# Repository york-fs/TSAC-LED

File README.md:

This board is based on the design by Rootthecause, whos original design can be accessed [here](https://github.com/Rootthecause/HVI)

Changes made (Listed in order to conform to the CERN Open Hardware Licence):
- The two connectors as input has been changed to a single molex microfit plus connector
- The output connector has been replaced with a molex microfit plus equivalent
- The DC/DC converter has been changed to a 12V one, in order for a 12V output
- The board has been restructured and more silkscreen elements have been added

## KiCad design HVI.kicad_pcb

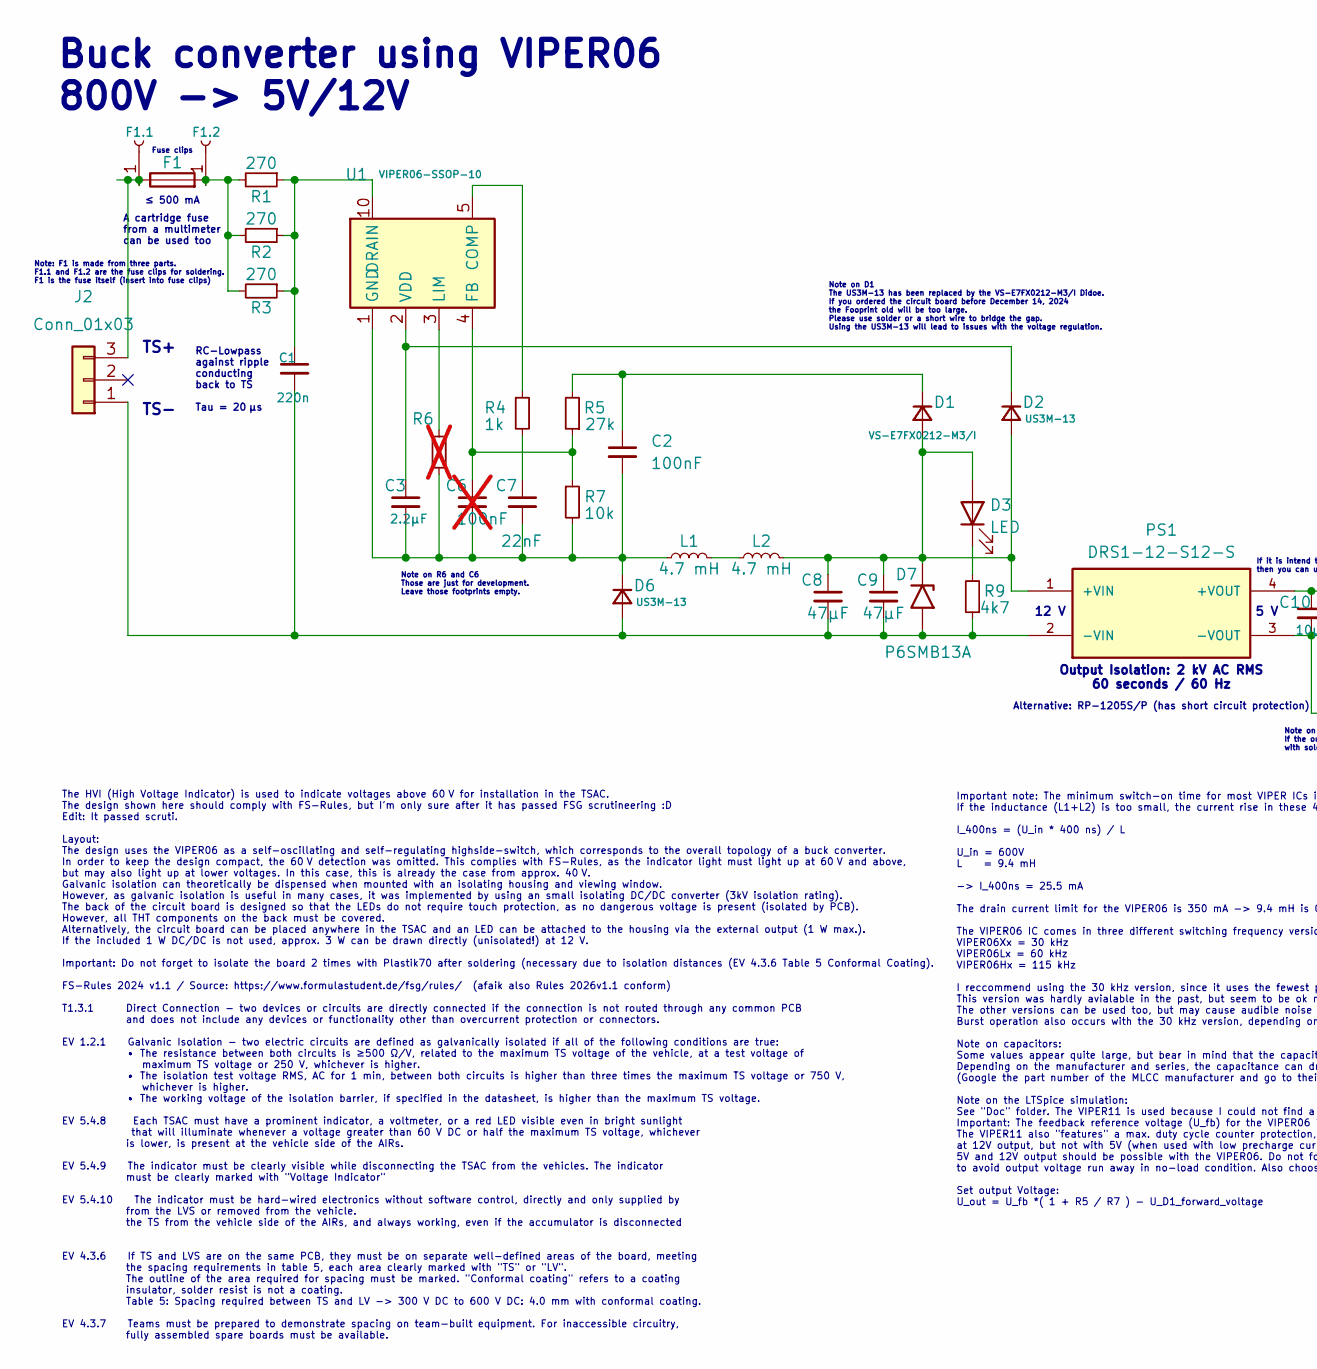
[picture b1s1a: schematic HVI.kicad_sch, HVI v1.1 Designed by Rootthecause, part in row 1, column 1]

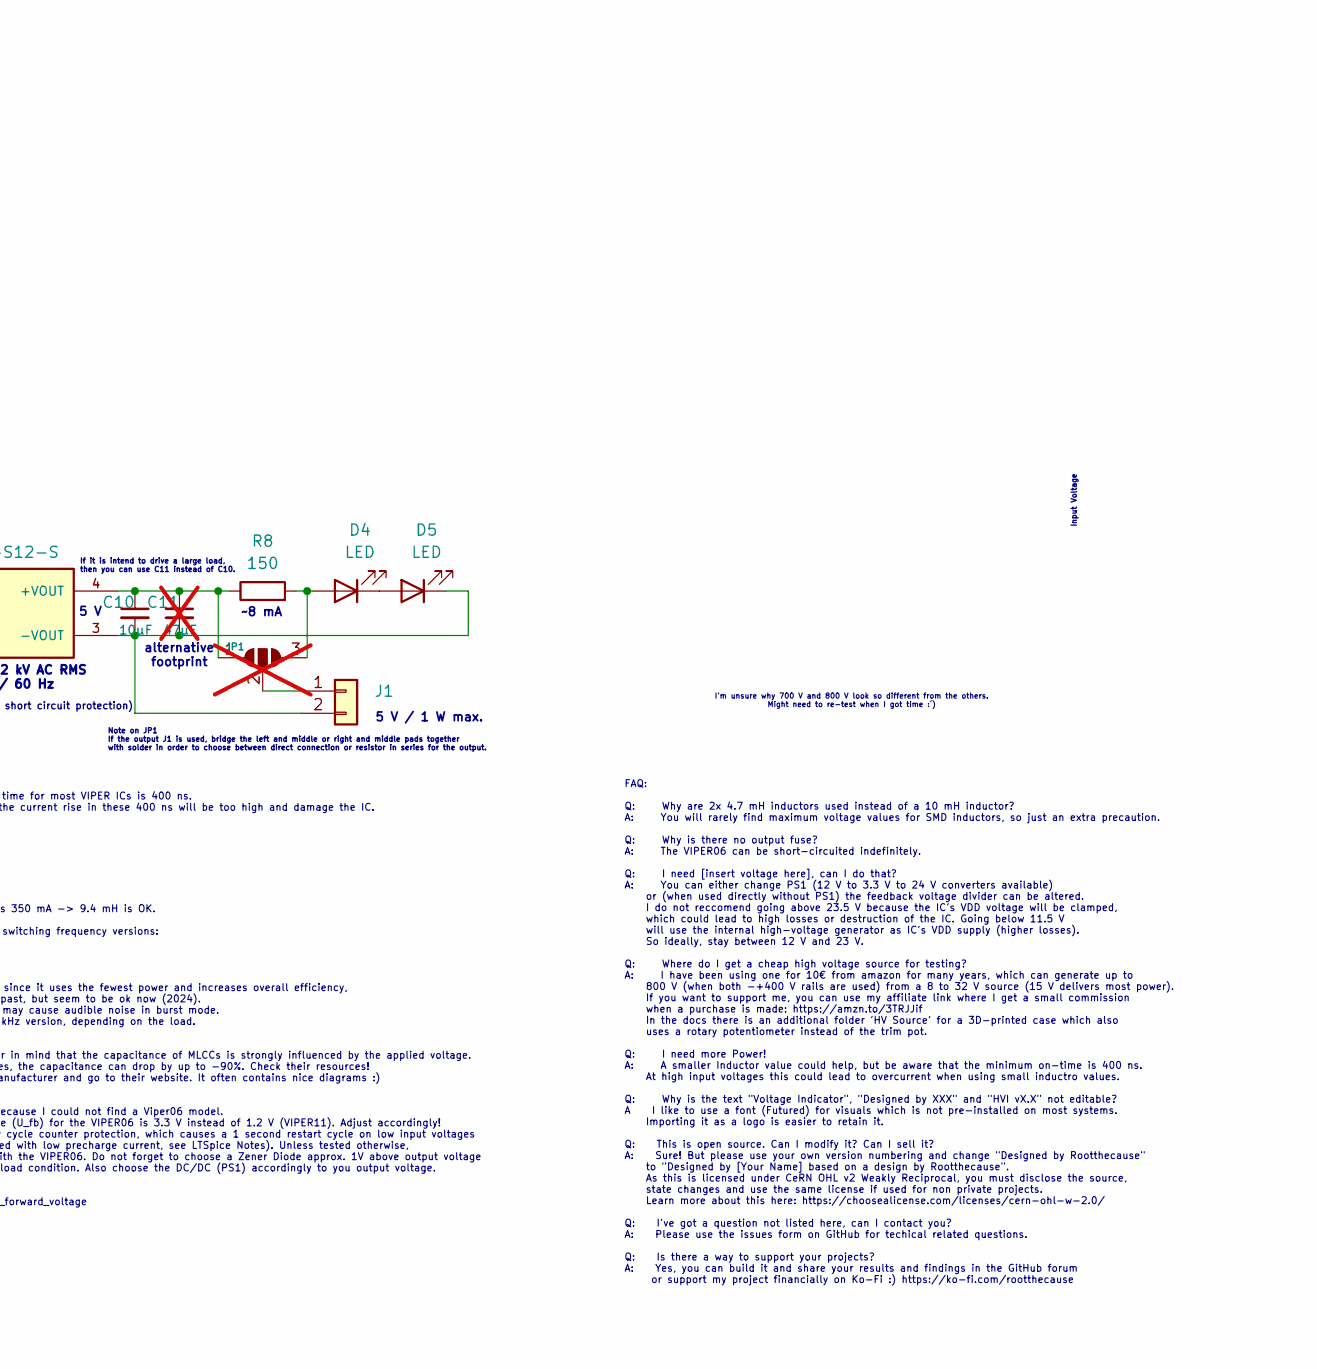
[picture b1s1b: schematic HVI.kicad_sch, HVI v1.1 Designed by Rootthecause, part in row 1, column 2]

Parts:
C1: 220n; C_2220_5650Metric; Mouser 810-C5750X7R2J224K
C2: 100nF; C_0603_1608Metric_Pad1.08x0.95mm_HandSolder; Mouser 81-GRM188R72A103MA1J
C3: 2.2µF; C_0603_1608Metric_Pad1.08x0.95mm_HandSolder; Mouser 963-UMK107BBJ225KA-T
C6: 100nF; C_0603_1608Metric_Pad1.08x0.95mm_HandSolder; not fitted
C7: 22nF; C_0603_1608Metric_Pad1.08x0.95mm_HandSolder; Mouser 80-C0603C223J3RAUTO
C8, C9: 47µF; C_1210_3225Metric_Pad1.33x2.70mm_HandSolder; Mouser 963-E32MAB5476MPNDTJ
C10: 10µF; C_0603_1608Metric_Pad1.08x0.95mm_HandSolder; Mouser 81-GRM188R6YA106MA3J
C11: 47µF; C_1210_3225Metric_Pad1.33x2.70mm_HandSolder; not fitted
D1: VS-E7FX0212-M3/I; D_SMF; Mouser 78-VS-E7FX0212-M3/I
D2, D6: US3M-13; D_SMC; Mouser 621-US3M-13
D3, D4, D5: LED; LED_0603_1608Metric_Pad1.05x0.95mm_HandSolder; Mouser 604-APTD1608LSURCK
D7: P6SMB13A; D_SMB; Mouser 652-P6SMB13A
F1: ≤ 500 mA, solder Fuse Clips F1.1 and F1.2 and ins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; Fuseholder_Clip-5x20mm_Keystone_3512_Inline_P23.62x7.27mm_D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; Mouser 530-0ADAC0250-BE
F1.1, F1.2: Fuse Clips; -; Mouser 576-01220083Z
J1: Conn_01x02; MolexMicrofitPlus1x2; Mouser 538-43650-0215
J2: Conn_01x03; MolexMicrofitPlus1x3
JP1: SolderJumper_3_Open; SolderJumper-3_P1.3mm_Open_RoundedPad1.0x1.5mm_NumberLabels; not fitted
L1, L2: 4.7 mH; L_Bourns_SRR1208_12.7x12.7mm; Mouser 652-SRR1208-472KL
PS1: DRS1-12-S12-S; DCDC-12v_12v-DRS1-12-S12-S; LCSC X
R1, R2, R3: 270; R_1206_3216Metric_Pad1.30x1.75mm_HandSolder; Mouser 755-KTR18EZPF2700
R4: 1k; R_0603_1608Metric_Pad0.98x0.95mm_HandSolder; Mouser 71-CRCW06031K00FKEE
R5: 27k; R_0603_1608Metric_Pad0.98x0.95mm_HandSolder; Mouser 603-AC0603FR-0727KL
R6: -; R_0603_1608Metric_Pad0.98x0.95mm_HandSolder; not fitted
R7: 10k; R_0603_1608Metric_Pad0.98x0.95mm_HandSolder; Mouser 603-AC0603JR-0710KL
R8: 150; R_0603_1608Metric_Pad0.98x0.95mm_HandSolder; Mouser 603-AC0603FR-10150RL
R9: 4k7; R_0603_1608Metric_Pad0.98x0.95mm_HandSolder; Mouser 603-RC0201FR-074K7L
U1: VIPER06-SSOP-10; SSOP-10_3.9x4.9mm_P1.00mm; Mouser 511-VIPER06XSTR

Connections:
unnamed: C1.1, R1.1, R2.1, R3.1, U1.6 (DRAIN), U1.7 (DRAIN), U1.8 (DRAIN), U1.9 (DRAIN), U1.10 (DRAIN)
unnamed: C7.1, R4.2
unnamed: C8.1, C9.1, D1.2 (A), D2.2 (A), D3.2 (A), D7.1 (A1), L2.2, PS1.1 (+VIN)
unnamed: C2.1, D1.1 (K), R5.2
unnamed: C3.1, D2.1 (K), U1.2 (VDD)
unnamed: D3.1 (K), R9.2
unnamed: D4.2 (A), JP1.3 (B), R8.2
unnamed: D4.1 (K), D5.2 (A)
unnamed: C10.2, C11.2, D5.1 (K), J1.2, PS1.3 (-VOUT)
unnamed: C1.2, C8.2, C9.2, D6.2 (A), D7.2 (A2), J2.1, PS1.2 (-VIN), R9.1
unnamed: C2.2, C3.2, C6.2, C7.2, D6.1 (K), L1.1, R6.2, R7.2, U1.1 (GND)
unnamed: F1.2, F1.2.1, R1.2, R2.2, R3.2
unnamed: J1.1, JP1.2 (C)
unnamed: F1.1, F1.1.1, J2.3
unnamed: C10.1, C11.1, JP1.1 (A), PS1.4 (+VOUT), R8.1
unnamed: L1.2, L2.1
unnamed: R4.1, U1.5 (COMP)
unnamed: C6.1, R5.1, R7.1, U1.4 (FB)
unnamed: R6.1, U1.3 (LIM)

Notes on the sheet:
If it is intend to drive a large load, then you can use C11 instead of C10.
I'm unsure why 700 V and 800 V look so different from the others. Might need to re-test when I got time :‘)
Buck converter using VIPER06 800V -> 5V/12V
FAQ: Q: Why are 2x 4.7 mH inductors used instead of a 10 mH inductor? A: You will rarely find maximum voltage values for SMD inductors, so just an extra precaution. Q: Why is there no output fuse? A: The VIPER06 can be short-circuited indefinitely. Q: I need [insert voltage here], can I do that? A: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
TS-
Alternative: RP-1205S/P (has short circuit protection)
5 V / 1 W max.
The HVI (High Voltage Indicator) is used to indicate voltages above 60 V for installation in the TSAC. The design shown here should comply with FS-Rules, but I'm only sure after it has passed FSG scrutineering :D Edit: It passed scruti. Layout: The design uses the VIPER06 as a self-oscillating and 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
Input Voltage
≤ 500 mA
Output Isolation: 2 kV AC RMS 60 seconds / 60 Hz
5 V
Note on R6 and C6 Those are just for development. Leave those footprints empty.
RC-Lowpass against ripple conducting back to TS Tau = 20 µs
~8 mA
Note: F1 is made from three parts. F1.1 and F1.2 are the fuse clips for soldering. F1 is the fuse itself (insert into fuse clips)
12 V
alternative footprint
Note on JP1 If the output J1 is used, bridge the left and middle or right and middle pads together with solder in order to choose between direct connection or resistor in series for the output.
Fuse clips
A cartridge fuse from a multimeter can be used too
Important note: The minimum switch-on time for most VIPER ICs is 400 ns. If the inductance (L1+L2) is too small, the current rise in these 400 ns will be too high and damage the IC. I_400ns = (U_in * 400 ns) / L U_in = 600V L = 9.4 mH -> I_400ns = 25.5 mA The drain current limit for the VIPER06 is 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
TS+
Note on D1 The US3M-13 has been replaced by the VS-E7FX0212-M3/I Didoe. If you ordered the circuit board before December 14, 2024 the Fooprint old will be too large. Please use solder or a short wire to bridge the gap. Using the US3M-13 will lead to issues with the voltage regulation.

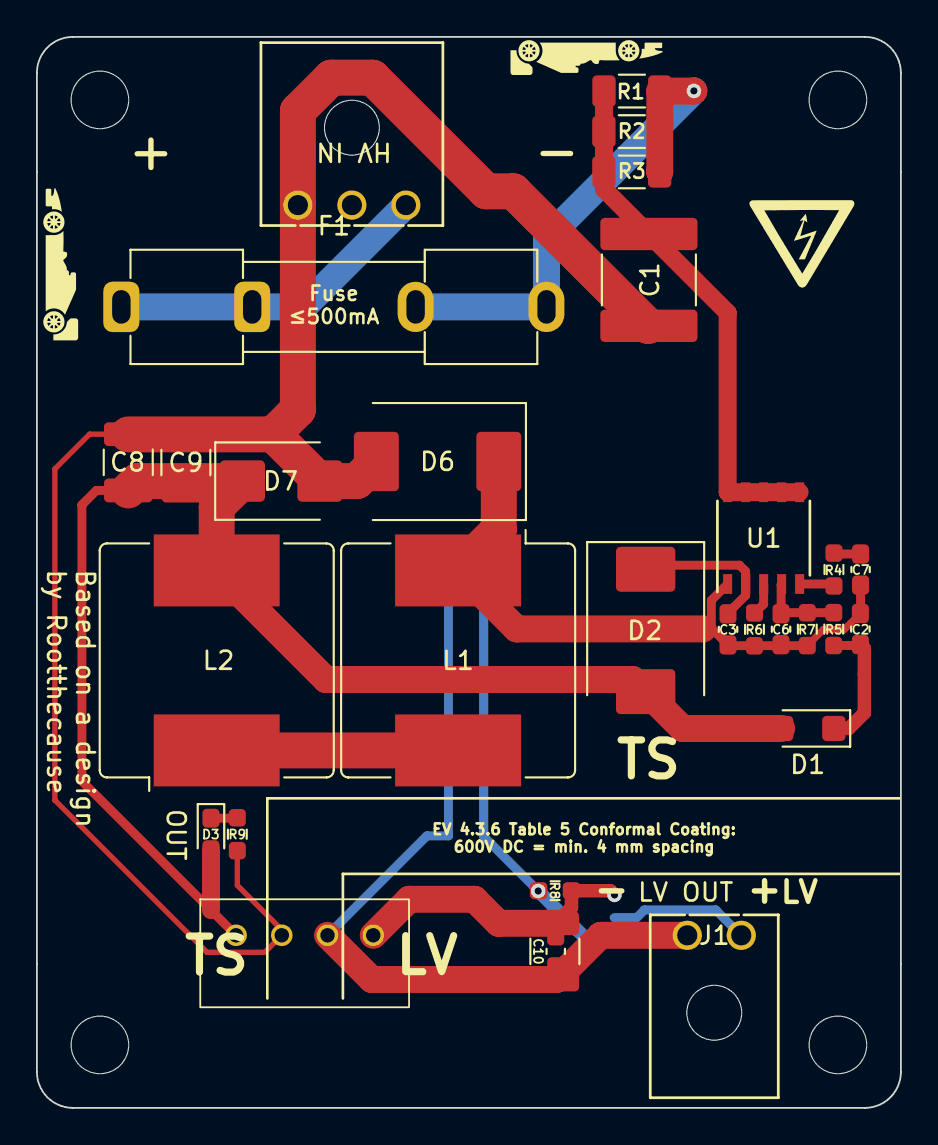
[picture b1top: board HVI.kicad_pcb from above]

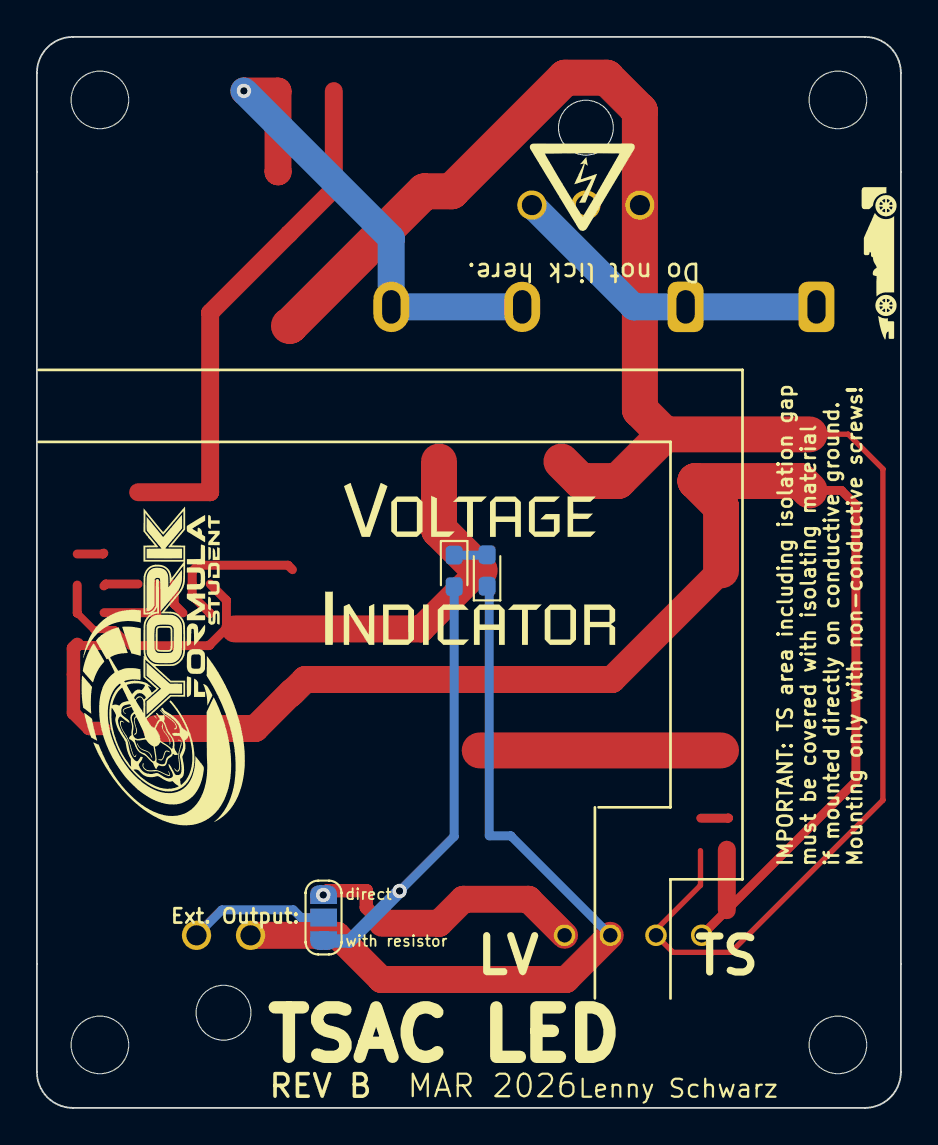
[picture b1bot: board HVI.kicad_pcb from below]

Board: 2 copper layers, 48.0 x 59.5 mm, 37 parts (3 on the bottom side), 19 nets.

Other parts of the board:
MK1, MK2, MK3, MK4: Mounting_Hole; MountingHole_3.2mm_M3_DIN965

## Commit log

2026-03-18 Changed the connectors to Molex MicrofitPlus
2026-03-18 Changed the DC/DC converter to 12V/12V, and updated the labels for the pin
2026-03-25 Added the footprint of the new DC/DC converter and moved around the PCB a tad
2026-03-25 Added silkscreen components, and ensured that it complied with the license
2026-03-25 Readme has been updated to conform with the license
2026-04-22 Changed the fuse
2026-04-22 Ensured it based
2026-04-22 Changed the size of a couple of traces

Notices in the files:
HVI.kicad_sch:
As this is licensed under CeRN OHL v2 Weakly Reciprocal, you must disclose the source,
state changes and use the same license if used for non private projects.
Learn more about this here: https://choosealicense.com/licenses/cern-ohl-w-2.0
